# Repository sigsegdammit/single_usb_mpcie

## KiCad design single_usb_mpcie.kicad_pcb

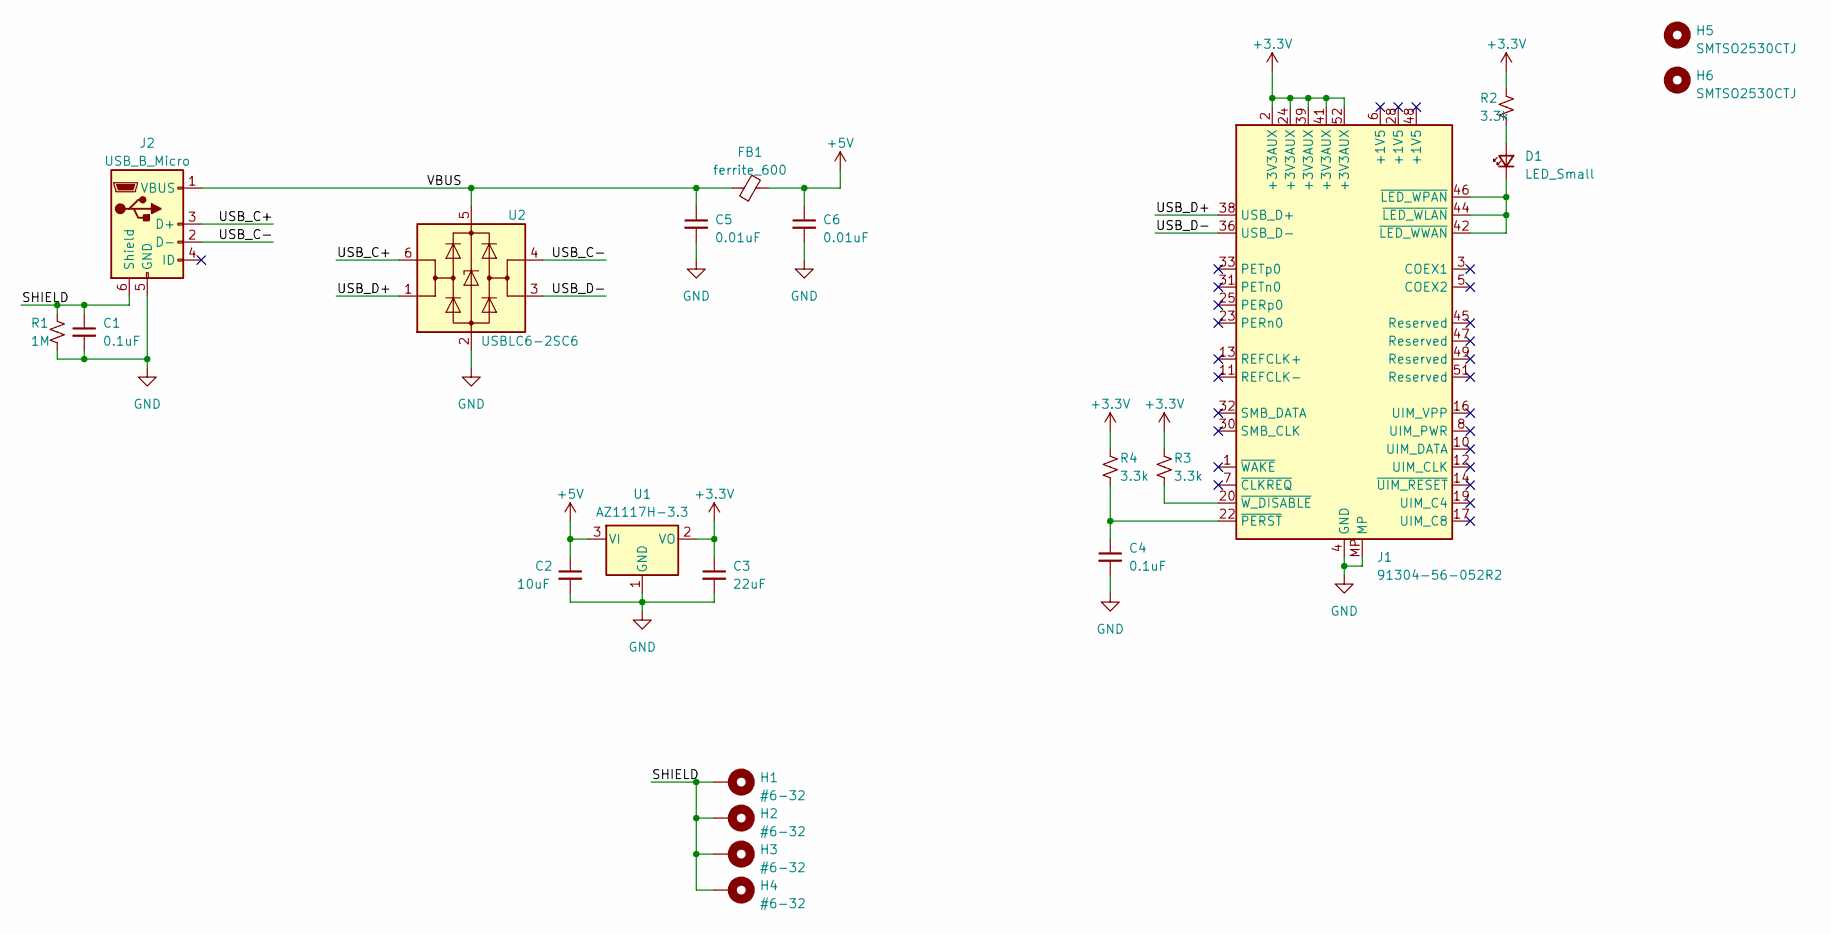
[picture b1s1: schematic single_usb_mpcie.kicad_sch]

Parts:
C1, C4: 0.1uF; C_0603_1608Metric; LCSC C14663
C2: 10uF; C_1206_3216Metric; LCSC C13585
C3: 22uF; C_1206_3216Metric; LCSC C12891
C5, C6: 0.01uF; C_0603_1608Metric; LCSC C57112
D1: LED_Small; LED_0603_1608Metric; LCSC C72041
FB1: ferrite_600; L_0603_1608Metric; LCSC C1017
H1, H2, H3, H4: #6-32; MountingHole_6-32_Pad
H5, H6: SMTSO2530CTJ; SMTSO25; LCSC C2915631
J1: 91304-56-052R2; BUS_PCI_Express_Mini_Full; LCSC C404121
J2: USB_B_Micro; USB_Mini-B_Wuerth_65100516121_Horizontal; LCSC C2681563
R1: 1M; R_0603_1608Metric; LCSC C22935
R2, R3, R4: 3.3k; R_0603_1608Metric; LCSC C22978
U1: AZ1117H-3.3; SOT-223-3_TabPin2; LCSC C92517
U2: USBLC6-2SC6; SOT-23-6; LCSC C7519

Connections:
+3.3V: C3.1, J1.2 (+3V3AUX), J1.24 (+3V3AUX), J1.39 (+3V3AUX), J1.41 (+3V3AUX), J1.52 (+3V3AUX), R2.1, R3.1, R4.1, U1.2 (VO)
+5V: C2.1, C6.1, FB1.2, U1.3 (VI)
/SHIELD: C1.1, H1.1, H2.1, H3.1, H4.1, J2.6 (Shield), R1.1
/USB_C+: J2.3 (D+), U2.6 (I/O1)
/USB_C-: J2.2 (D-), U2.4 (I/O2)
/USB_D+: J1.38 (USB_D+), U2.1 (I/O1)
/USB_D-: J1.36 (USB_D-), U2.3 (I/O2)
/VBUS: C5.1, FB1.1, J2.1 (VBUS), U2.5 (VBUS)
GND: C1.2, C2.2, C3.2, C4.2, C5.2, C6.2, J1.4 (GND), J1.9 (GND), J1.15 (GND), J1.18 (GND), J1.21 (GND), J1.26 (GND), J1.27 (GND), J1.29 (GND), J1.34 (GND), J1.35 (GND), J1.37 (GND), J1.40 (GND), J1.43 (GND), J1.50 (GND), J1.MP, J2.5 (GND), R1.2, U1.1 (GND), U2.2 (GND)
unnamed: D1.2 (A), R2.2
unnamed: D1.1 (K), J1.42 (~LED_WWAN), J1.44 (~LED_WLAN), J1.46 (~LED_WPAN)
unnamed: C4.1, J1.22 (~PERST), R4.2
unnamed: J1.20 (~W_DISABLE), R3.2

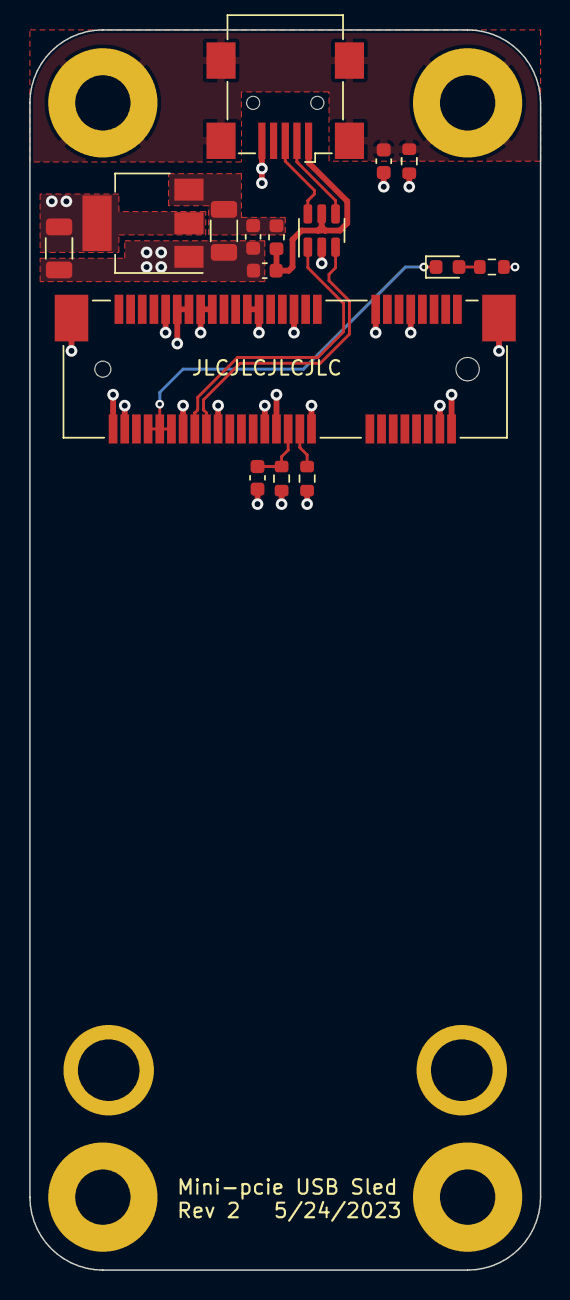
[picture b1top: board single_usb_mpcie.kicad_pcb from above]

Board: 4 copper layers, 35.0 x 85.0 mm, 22 parts (0 on the bottom side), 13 nets.

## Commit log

2023-05-04 Initial design of single USB to mini-pcie adapter
2023-05-04 Add 3d model for standoffs
2023-05-15 Change mounting holes to #6-32
2023-05-25 Add ESD on USB lines. Add noise filtering to VBUS. Change to a 4-layer board with ground / power planes.
2023-05-25 Rev silkscreen. Tweak grounds
